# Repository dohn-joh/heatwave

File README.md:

***

Heatwave is a 36-key wireless, curved alpha stagger keyboard with integrated lever keycaps.

[PCB](pcb)

[Case files](case)

[swell keycaps](https://github.com/dohn-joh/swell-keycaps)

[ZMK Module](https://github.com/dohn-joh/heatwave-zmk-module)

[video](https://vimeo.com/1097657262)

***

## BOM
|Part|Quantity|Link|
|-|:-:|-|
|Microcontroller: Xiao nRF52840 Plus|1|https://www.seeedstudio.com/Seeed-Studio-XIAO-nRF52840-Plus-p-6359.html|
|Battery: 301230 with molex pico ezmate connector|1|Select L0040. https://www.aliexpress.us/item/3256802674181210.html|
|Battery connector: molex pico ezmate 1x02|1|Select 2P. https://www.aliexpress.us/item/3256805726980487.html|
|Reset button: EVQPUC02K|1|https://www.aliexpress.us/item/2251832616044011.html|
|Diodes: BAV70 (SOT-23)|18|https://www.amazon.com/dp/B079KKPMBT|
|M2 heatset inserts (OD:3.2, Height: 2-3mm)|6|https://www.aliexpress.us/item/3256806286387666.html|
|M2 screws 5mm, flat head|6|https://www.aliexpress.us/item/3256805084387535.html|
|Switches|36|Your choice of choc v2. Recommended: Lofree hades or any POM silent linear switch|
|Kailh Choc PG1350 Hot Swap Sockets|36|https://www.aliexpress.us/item/3256803687338432.html|
|Rubber feet 6mm diameter x 1mm height|6|Unfortunately this vendor only lists higher quantities now. If the price is too high, maybe try contacting the vendor for smaller quantities. https://www.aliexpress.com/store/1100976482|
|Keycaps|36|https://github.com/dohn-joh/swell-keycaps|
|Magnetic USB connector/cable: Netdot Gen10|1|https://www.amazon.com/dp/B07MBD3FZD|
|Steel dressmaker pins, Size 20 (1-1/4")|2|https://www.amazon.com/dp/B003W0TIH6|

## Build notes
Depending on the quality of the MJF prints:
- You will likely need to postprocess the lever keycaps in order for them to actuate properly. (This is by design. It is much easier to remove material than to add.) Postprocessing is very straightforward. All you need is a small strip of 80 grit sandpaper. Wet the sandpaper and lightly sand the underside of the lever keycap, then test to see if it actuates. If it does not, continue to sand and test until you get the desired thickness. If you want to be super accurate, you can use a caliper to measure the thickness after each sanding to match the thickness of both lever keycaps.
- If the dressmaker pin is not friction fitting, you can either glue the head in place, or carefully use a soldering iron to heatset it in place.

***

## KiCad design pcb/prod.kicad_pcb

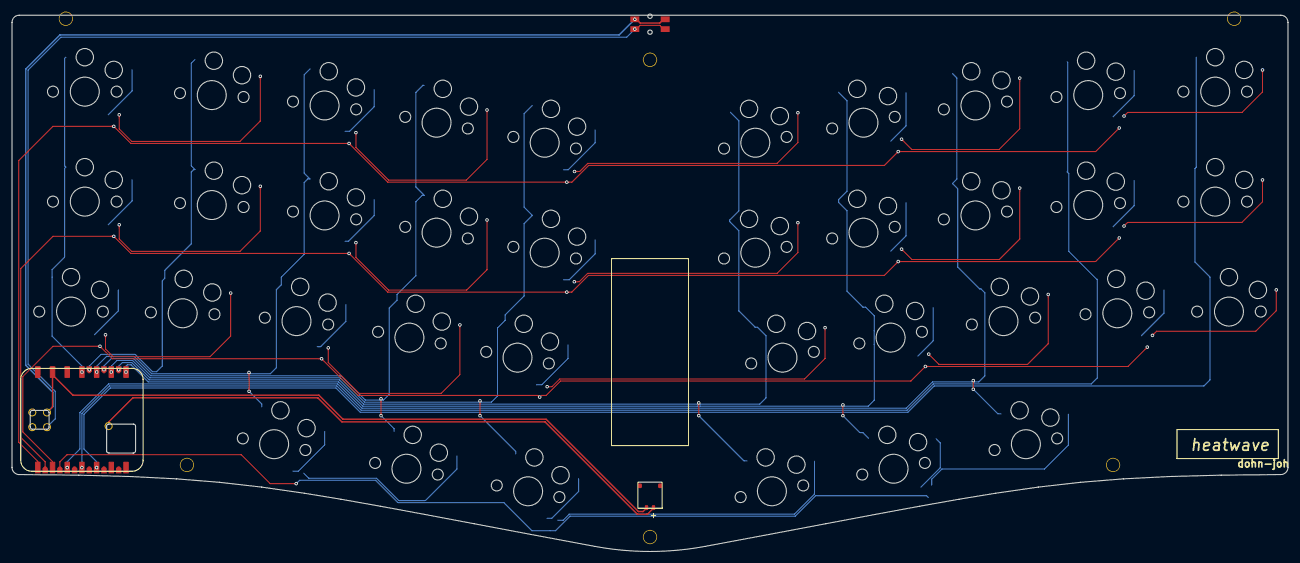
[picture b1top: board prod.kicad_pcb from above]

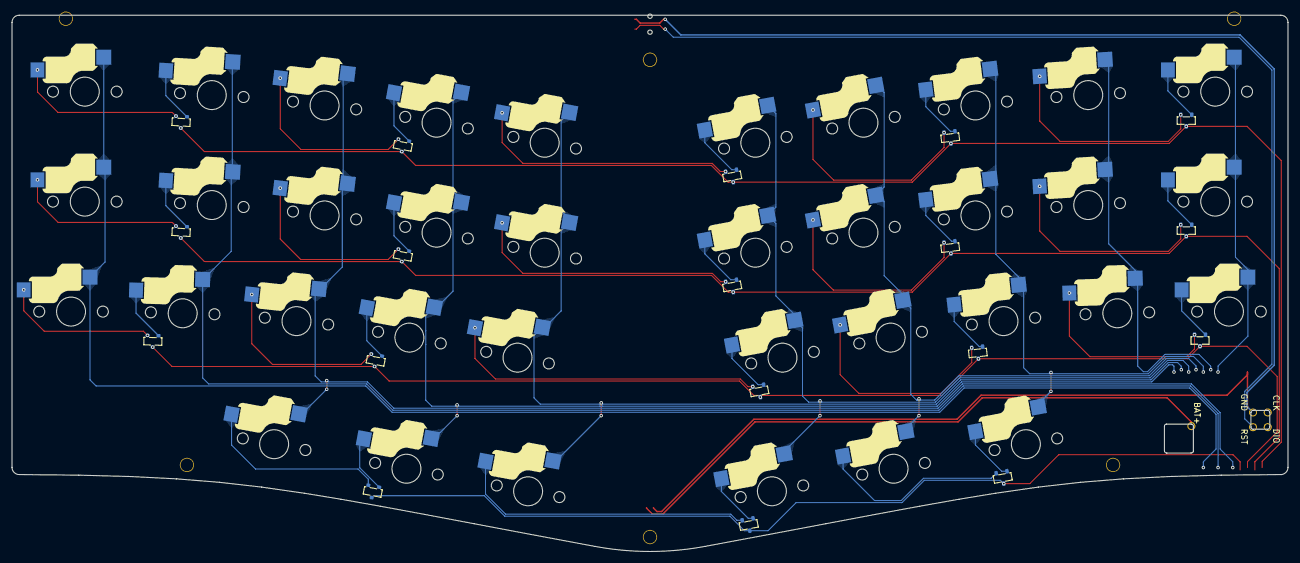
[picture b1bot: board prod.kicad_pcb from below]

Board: 2 copper layers, 220.4 x 92.6 mm, 64 parts (18 on the bottom side), 53 nets.

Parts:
D1, D2, D3, D4, D5, D6, D7, D8, D9, D10, D11, D12, D13, D14, D15, D16, D17, D18: SOT-23
EC1: pcb_shape
H1, H2, H3, H4, H5, H6: mounting_hole
MCU1: xiao_plus_smd_prod
SW1, SW2: choc
SW3, SW4, SW5, SW6, SW7, SW8, SW9, SW10, SW11, SW12, SW13, SW14, SW15, SW16, SW17, SW18, SW19, SW20, SW21, SW22, SW23, SW24, SW25, SW26, SW27, SW28, SW29, SW30: sw_choc_1u
SW31, SW32, SW33, SW34, SW35, SW36: sw_choc_1.25u
XX1: sw_reset_side
XX2: conn_molex_pico_front

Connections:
BAT+: MCU1.28, XX2.1
C1: MCU1.11, SW19.1, SW31.1, SW33.1
C2: MCU1.23, SW3.1, SW11.1, SW20.1
C3: MCU1.10, SW1.1, SW4.1, SW12.1, SW21.1
C4: MCU1.22, SW5.1, SW13.1, SW22.1, SW29.1
C5: MCU1.9, SW6.1, SW14.1, SW23.1, SW35.1
C6: MCU1.21, SW10.1, SW18.1, SW28.1, SW36.1
C7: MCU1.8, SW9.1, SW17.1, SW27.1, SW30.1
C8: MCU1.3, SW2.1, SW8.1, SW16.1, SW26.1
C9: MCU1.4, SW7.1, SW15.1, SW25.1
C10: MCU1.5, SW24.1, SW32.1, SW34.1
GND: MCU1.13, MCU1.27, XX1.1, XX1.3, XX2.2
R1: D1.3, D2.3, D3.3, D12.3, D13.3, MCU1.1
R2: D4.3, D5.3, D6.3, D14.3, D15.3, MCU1.15
R3: D7.3, D8.3, D9.3, D16.3, D17.3, MCU1.2
R4: D10.3, D11.3, D18.3, MCU1.16
RST: MCU1.26, XX1.2, XX1.4
a_home: D4.1, SW33.2
b_bottom: D9.1, SW23.2
base_thumb: D10.2, SW29.2
c_bottom: D8.1, SW21.2
d_home: D5.1, SW12.2
e_top: D2.1, SW4.2
ext_thumb: D11.1, SW35.2
f_home: D5.2, SW13.2
flex_thumb: D10.1, SW1.2
g_home: D6.1, SW14.2
mirror_a_home: D14.2, SW34.2
mirror_b_bottom: D9.2, SW28.2
mirror_base_thumb: D18.1, SW30.2
mirror_c_bottom: D17.2, SW26.2
mirror_d_home: D15.2, SW16.2
mirror_e_top: D13.2, SW8.2
mirror_ext_thumb: D11.2, SW36.2
mirror_f_home: D15.1, SW17.2
mirror_flex_thumb: D18.2, SW2.2
mirror_g_home: D6.2, SW18.2
mirror_q_top: D12.2, SW32.2
mirror_r_top: D13.1, SW9.2
mirror_s_home: D14.1, SW15.2
mirror_t_top: D3.2, SW10.2
mirror_v_bottom: D17.1, SW27.2
mirror_w_top: D12.1, SW7.2
mirror_x_bottom: D16.1, SW25.2
mirror_z_bottom: D16.2, SW24.2
q_top: D1.1, SW31.2
r_top: D2.2, SW5.2
s_home: D4.2, SW11.2
t_top: D3.1, SW6.2
v_bottom: D8.2, SW22.2
w_top: D1.2, SW3.2
x_bottom: D7.2, SW20.2
z_bottom: D7.1, SW19.2

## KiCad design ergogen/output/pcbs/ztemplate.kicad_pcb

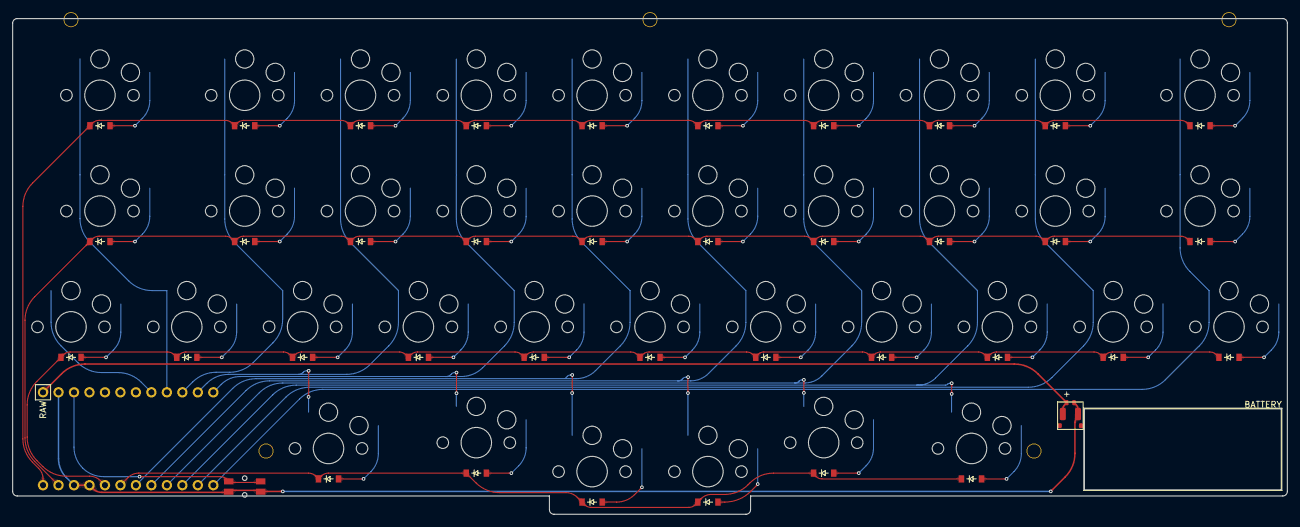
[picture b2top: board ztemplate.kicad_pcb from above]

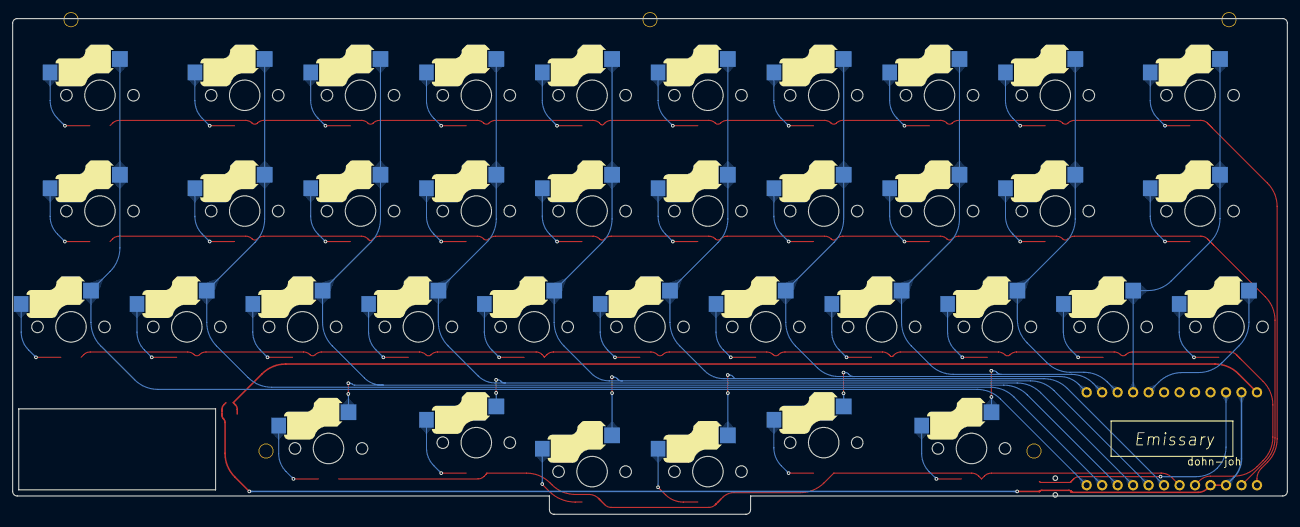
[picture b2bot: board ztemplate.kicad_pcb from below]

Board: 2 copper layers, 209.2 x 81.3 mm, 83 parts (37 on the bottom side), 55 nets.

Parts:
CONN1: conn_molex_pico_front
D1, D2, D3, D4, D5, D6, D7, D8, D9, D10, D11, D12, D13, D14, D15, D16, D17, D18, D19, D20, D21, D22, D23, D24, D25, D26, D27, D28, D29, D30, D31, D32, D33, D34, D35, D36, D37: ComboDiode
H1, H2, H3, H4, H5: mounting_hole
MCU1: supermini_front
PAD1: battery_pads
S1, S2, S3, S4, S5, S6, S7, S8, S9, S10, S11, S12, S13, S14, S15, S16, S17, S18, S19, S20, S21, S22, S23, S24, S25, S26, S27, S28, S29, S30, S31, S32, S33, S34, S35, S36, S37: switch_choc_v1_v2_filled
SW1: reset_button; sw_reset_side

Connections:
C0: MCU1.8, S21.1
C1: MCU1.9, S1.1, S11.1, S22.1
C2: MCU1.10, S2.1, S12.1, S23.1
C3: MCU1.11, S3.1, S13.1, S24.1, S32.1
C4: MCU1.12, S4.1, S14.1, S25.1, S33.1
C5: MCU1.18, S5.1, S15.1, S26.1, S34.1
C6: MCU1.17, S6.1, S16.1, S27.1, S35.1
C7: MCU1.16, S7.1, S17.1, S28.1, S36.1
C8: MCU1.15, S8.1, S18.1, S29.1, S37.1
C9: MCU1.14, S9.1, S19.1, S30.1
C10: MCU1.13, S10.1, S20.1, S31.1
GND: CONN1.2, MCU1.2, MCU1.21, MCU1.22, PAD1.2, SW1.1, SW1.3
R1: D1.1, D2.1, D3.1, D4.1, D5.1, D6.1, D7.1, D8.1, D9.1, D10.1, MCU1.24
R2: D11.1, D12.1, D13.1, D14.1, D15.1, D16.1, D17.1, D18.1, D19.1, D20.1, MCU1.23
R3: D21.1, D22.1, D23.1, D24.1, D25.1, D26.1, D27.1, D28.1, D29.1, D30.1, D31.1, MCU1.20
R4: D32.1, D33.1, D34.1, D35.1, D36.1, D37.1, MCU1.19
RAW: CONN1.1, MCU1.1, PAD1.1
RST: MCU1.3, SW1.2, SW1.4
a_home: D11.2, S11.2
b_bottom: D26.2, S26.2
base2_thumb: D36.2, S36.2
base_thumb: D33.2, S33.2
c_bottom: D24.2, S24.2
comma_bottom: D29.2, S29.2
d_home: D13.2, S13.2
dot_bottom: D30.2, S30.2
e_top: D3.2, S3.2
ext2_thumb: D35.2, S35.2
ext_thumb: D34.2, S34.2
extra_bottom: D21.2, S21.2
f_home: D14.2, S14.2
flex2_thumb: D37.2, S37.2
flex_thumb: D32.2, S32.2
g_home: D15.2, S15.2
h_home: D16.2, S16.2
i_top: D8.2, S8.2
j_home: D17.2, S17.2
k_home: D18.2, S18.2
l_home: D19.2, S19.2
m_bottom: D28.2, S28.2
n_bottom: D27.2, S27.2
o_top: D9.2, S9.2
p_top: D10.2, S10.2
q_top: D1.2, S1.2
r_top: D4.2, S4.2
s_home: D12.2, S12.2
semi_home: D20.2, S20.2
slash_bottom: D31.2, S31.2
t_top: D5.2, S5.2
u_top: D7.2, S7.2
v_bottom: D25.2, S25.2
w_top: D2.2, S2.2
x_bottom: D23.2, S23.2
y_top: D6.2, S6.2
z_bottom: D22.2, S22.2

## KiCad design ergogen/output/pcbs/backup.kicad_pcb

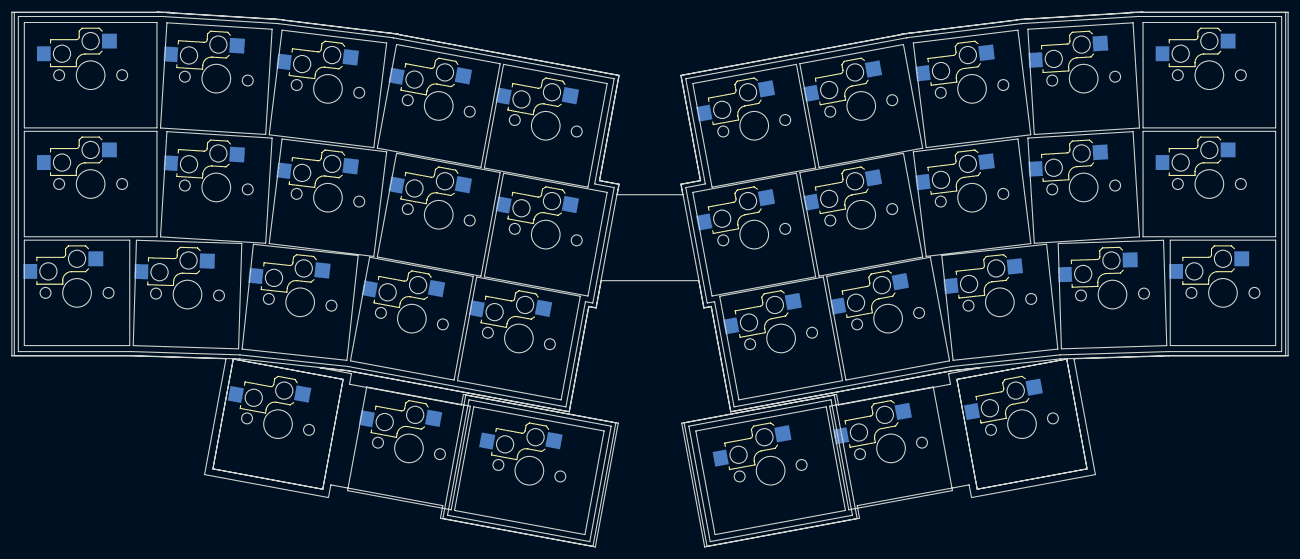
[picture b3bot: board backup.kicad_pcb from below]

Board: 2 copper layers, 222.8 x 93.4 mm, 36 parts (36 on the bottom side), 5 nets, no tracks yet.

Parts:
S1, S2, S3, S4, S5, S6, S7, S8, S9, S10, S11, S12, S13, S14, S15, S16, S17, S18, S19, S20, S21, S22, S23, S24, S25, S26, S27, S28, S29, S30, S31, S32, S33, S34, S35, S36: switch_choc_v1_v2

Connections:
C1: S1.1, S6.1, S11.1, S16.1, S21.1, S26.1
C2: S2.1, S7.1, S12.1, S17.1, S22.1, S27.1
C3: S3.1, S8.1, S13.1, S18.1, S23.1, S28.1, S31.1, S34.1
C4: S4.1, S9.1, S14.1, S19.1, S24.1, S29.1, S32.1, S35.1
C5: S5.1, S10.1, S15.1, S20.1, S25.1, S30.1, S33.1, S36.1

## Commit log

2025-04-10 fixed xiao arcs in ergogen fp
2025-04-26 updated footprint models
2025-04-29 update file name
2025-06-30 release
2025-07-01 added lever keycap
2025-07-01 copy kicad pcb to pcb folder
2025-07-01 cleanup
2025-07-21 add BOM
2025-07-21 fix build notes
2025-08-21 add didoes to BOM
